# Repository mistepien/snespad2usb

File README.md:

# snespad2usb
SNES gampepad adapter to USB.

<a href="https://github.com/mistepien/snespad2usb/blob/main/snespad2usb.pdf">Adapter</a> is actually a shield for 
<a href="https://learn.sparkfun.com/tutorials/pro-micro--fio-v3-hookup-guide/hardware-overview-pro-micro">Arduino Pro Micro based on ATmega 32U4</a>.

ATmega 32U4 has a hardware support for fullspeed USB, thus <a href="https://wiki.archlinux.org/title/mouse_polling_rate">polling rate 1000Hz</a> is not an issue for that chip.

You can use the <a href="https://github.com/mistepien/snespad2usb/tree/main/production">gerber file<a> to order the PCB.

Attached <a href="https://github.com/mistepien/snespad2usb/tree/main/firmware">code</a> uses port registers so that is quite efficient. The code was tested with <a href="https://www.8bitdo.com/sn30-wireless-for-original-snes-sfc/">SN30 2.4g wireless gamepad for original SNES/SFC</a> and original SNES and SFC gamepads. Everything works flawless!

One footprint is not trivial: SNES gamapad socket (<b>J1</b>). Footprint is DIY.

<b>J2</b> is redundant -- you can use it to add some new features like autofire switch or sth.

Sometimes during uploading code to Arduino board you may face some issues -- then you will need to use RESET -- so <b>SW1</b> can be useful if you like to develope your own code.

SW2 can be usefull to have a so-called "Hot key" -- you can need it eg. in Batocera.

LED D1 shows is SNES gamepad connected at all. LED D2 is just a status LED (turn on in setup() function of firmware).

BOM:
| Qty	| Reference(s) | Description |
|-----|--------------|-------------|
|2 | D1, D2 | LEDs 3mm |  
|1 | J1| SNES gamepad make connector |
|1 | J2| 2x4 Pinheader. pitch terminal: 2.54mm |
|1 | R1, R2 | resistors for D1 and D2 |
|1 | R3 | 10KΩ PULL-UP resistor for DATA gamepad pin |
|1 | SW1,SW2 | Tact switches from Arduino breadboard projects |
|1 | U1 | DIP20 socket (width 15.24mm) + <a href="https://learn.sparkfun.com/tutorials/pro-micro--fio-v3-hookup-guide/hardware-overview-pro-micro">Arduino Pro Micro</a> |

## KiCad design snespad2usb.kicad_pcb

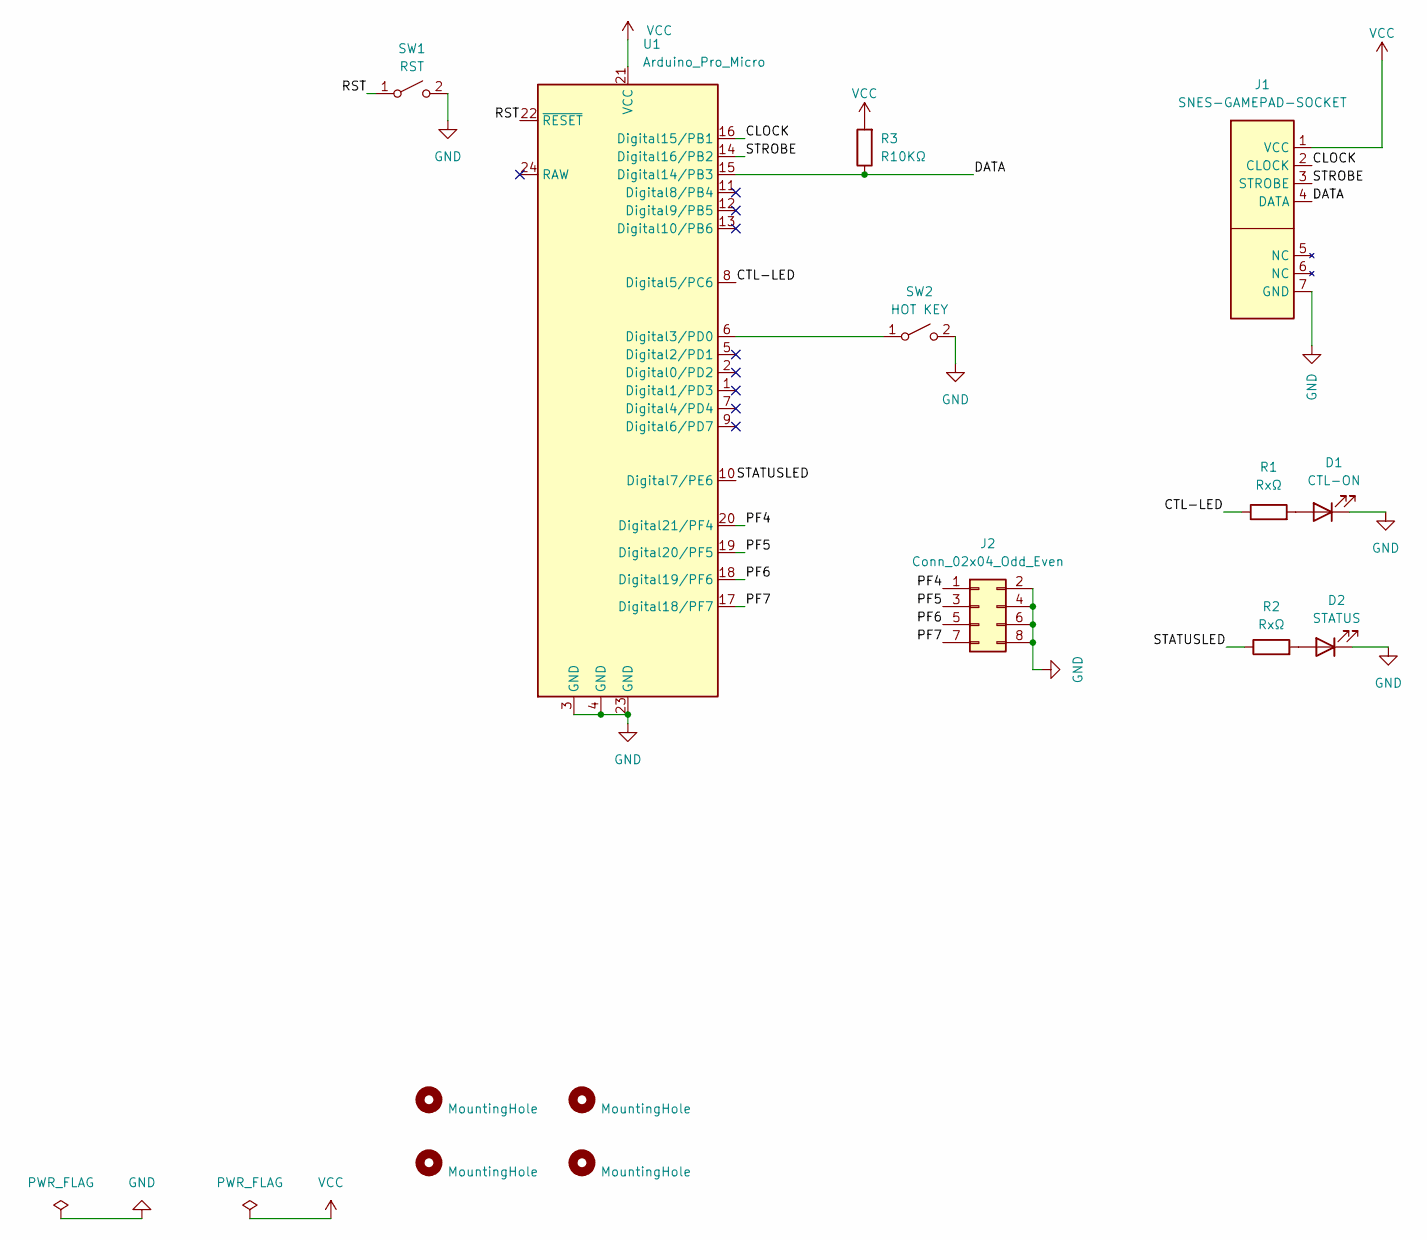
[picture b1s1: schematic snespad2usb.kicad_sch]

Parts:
D1: CTL-ON; LED_D3.0mm_Oval
D2: STATUS; LED_D3.0mm_Oval
H1, H2, H3, H4: MountingHole; MountingHole_3.5mm
J1: SNES-GAMEPAD-SOCKET; SNES_gamepad_connector_L_horizontal
J2: Conn_02x04_Odd_Even; PinHeader_2x04_P2.54mm_Vertical
R1, R2: RxΩ; R_Axial_DIN0207_L6.3mm_D2.5mm_P10.16mm_Horizontal_Oval
R3: R10KΩ; R_Axial_DIN0207_L6.3mm_D2.5mm_P10.16mm_Horizontal_Oval
SW1: RST; SW_PUSH_6mm_H4.3mm
SW2: HOT KEY; SW_PUSH_6mm_H4.3mm
U1: Arduino_Pro_Micro; DIP-24_W15.24mm_Socket_LongPads

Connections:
/CLOCK: J1.2 (CLOCK), U1.16 (Digital15/PB1)
/CTL-LED: R1.1, U1.8 (Digital5/PC6)
/DATA: J1.4 (DATA), R3.1, U1.15 (Digital14/PB3)
/PF4: J2.1, U1.20 (Digital21/PF4)
/PF5: J2.3, U1.19 (Digital20/PF5)
/PF6: J2.5, U1.18 (Digital19/PF6)
/PF7: J2.7, U1.17 (Digital18/PF7)
/RST: SW1.1 (A), U1.22 (~RESET)
/STATUSLED: R2.1, U1.10 (Digital7/PE6)
/STROBE: J1.3 (STROBE), U1.14 (Digital16/PB2)
GND: D1.1 (K), D2.1 (K), J1.7 (GND), J2.2, J2.4, J2.6, J2.8, SW1.2 (B), SW2.2 (B), U1.3 (GND), U1.4 (GND), U1.23 (GND)
unnamed: D1.2 (A), R1.2
unnamed: D2.2 (A), R2.2
unnamed: SW2.1 (A), U1.6 (Digital3/PD0)
VCC: J1.1 (VCC), R3.2, U1.21 (VCC)

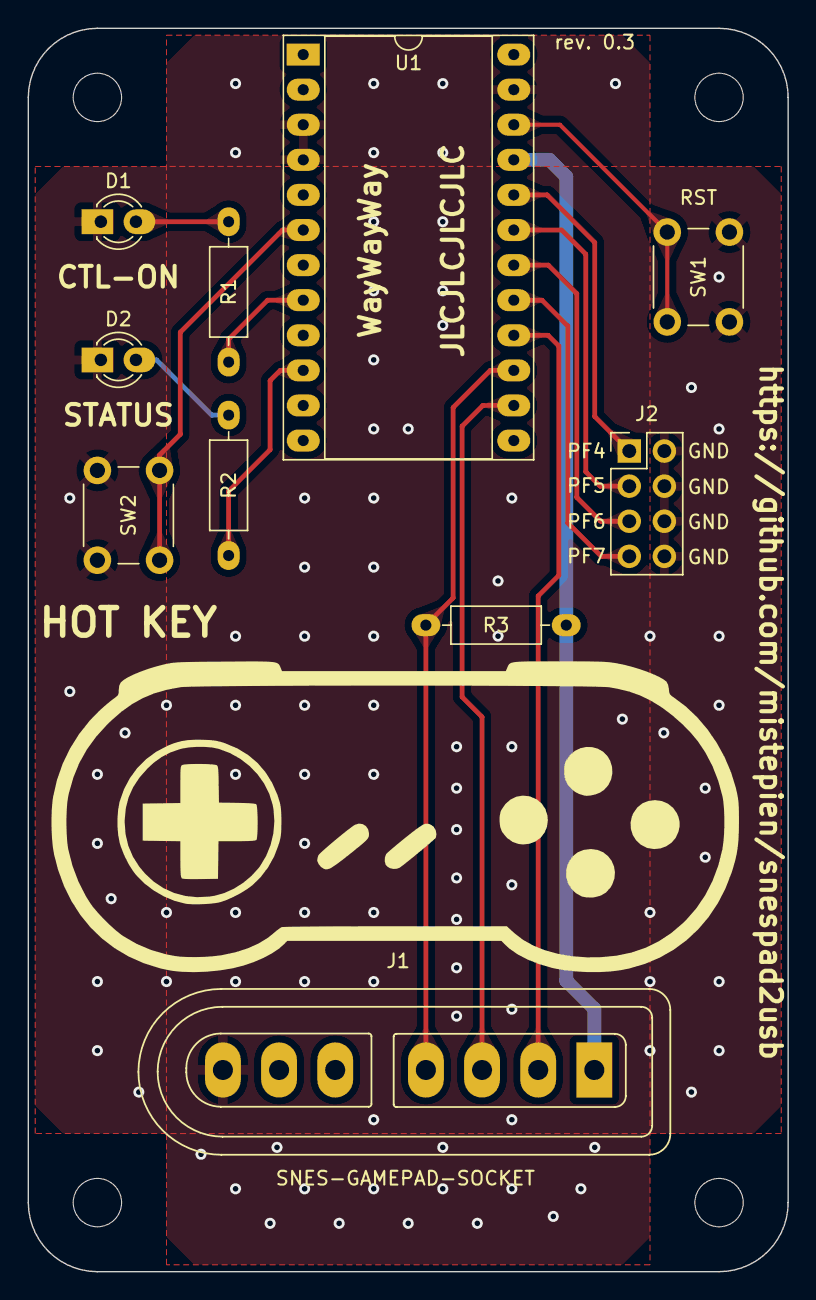
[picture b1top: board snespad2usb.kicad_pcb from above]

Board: 2 copper layers, 55.0 x 90.0 mm, 14 parts (0 on the bottom side), 15 nets.

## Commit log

2024-07-12 README.md initial upload
2024-07-12 initial upload
2024-07-12 PCB Rev. 0.3
2024-07-12 firmware files
2024-07-12 footprints
2024-07-12 symbols
2025-09-09 real update
